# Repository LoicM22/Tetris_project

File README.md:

# Tetris_project

The goal of this project was to create a wireless controller to a Tetris game which is coding in Python. 
All the steps for the creation of this project are detailed on "final_notice_tetris_project.pdf".

# Details of each folder

This repository is divided in 5 parts :

  - Assembly_of_the_controller : the assembly instructions and all the drawings of the parts of the controller
  - How_to_play : details of the movements of the game in fr and eng
  - PCB : Kicad files of the PCB made for the LED of the controller
  - Prog_Rasp : The code to put in the Raspberry and the instructions
  - Prog_Arduino : The code to put in the Arduino and tests for the state machine

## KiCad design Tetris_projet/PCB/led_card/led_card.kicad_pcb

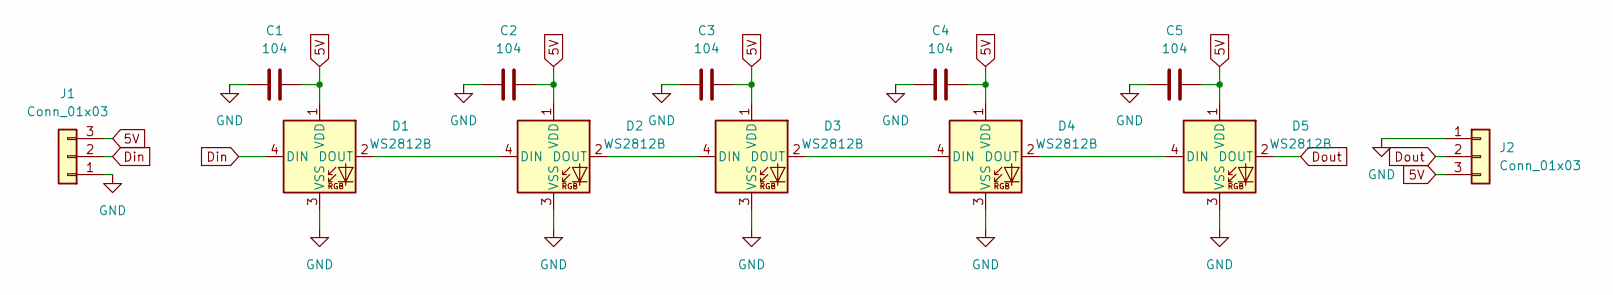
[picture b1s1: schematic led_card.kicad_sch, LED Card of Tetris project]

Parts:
C1, C2, C3, C4, C5: 104; C_0603_1608Metric_Pad1.08x0.95mm_HandSolder
D1, D2, D3, D4, D5: WS2812B; LED_WS2812B_PLCC4_5.0x5.0mm_P3.2mm
J1, J2: Conn_01x03; PinHeader_1x03_P2.54mm_Vertical

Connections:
5V: C1.1, C2.1, C3.1, C4.1, C5.1, D1.1 (VDD), D2.1 (VDD), D3.1 (VDD), D4.1 (VDD), D5.1 (VDD), J1.3, J2.3
Din: D1.4 (DIN), J1.2
Dout: D5.2 (DOUT), J2.2
GND: C1.2, C2.2, C3.2, C4.2, C5.2, D1.3 (VSS), D2.3 (VSS), D3.3 (VSS), D4.3 (VSS), D5.3 (VSS), J1.1, J2.1
unnamed: D1.2 (DOUT), D2.4 (DIN)
unnamed: D2.2 (DOUT), D3.4 (DIN)
unnamed: D3.2 (DOUT), D4.4 (DIN)
unnamed: D4.2 (DOUT), D5.4 (DIN)

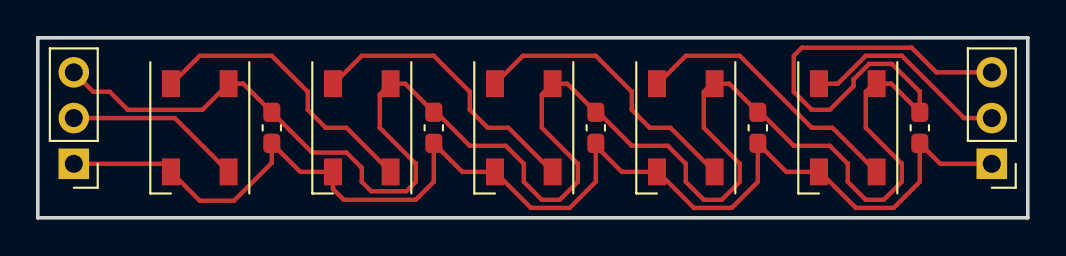
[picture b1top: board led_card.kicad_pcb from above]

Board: 2 copper layers, 55.0 x 10.0 mm, 12 parts (0 on the bottom side), 8 nets.

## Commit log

2022-01-10 Create Prog_Raspberry
2022-02-01 Update tuto_tetris_raspberry
